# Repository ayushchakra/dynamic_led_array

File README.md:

develoment steps:
1. create very basic tester board with serial connections, USBASP connections, and some debug LEDs. this will validate the USBasp pipeline(first test with the arduino IDE), and then enable us to test with the rust toolchain - also might be nice to include a small version of the programmable led array
2. in parallel, develop the schematic for the final PCB, not shipping it until phase 1. PCB has been fully validated

- phase 1 also serves as a tester platformthat can be used while debugging any hardware issues with phase 2. (essentially, instead of hardware commands, send the corresponding action over serial, this can be intercepted by a hardware visualizer on a computer to "simulate" the hardware

- phase 1 can use the LED Driver eval board (just one) with one LED array to serve as a testing platform, for future iterations, the chip can be integrated into the carrier board

LED array options:
|Link	|Communication Protocol	|Price|Daisy Chain?|
|-------|-----------------------|-----|------------|
[16x16](https://www.amazon.com/BTF-LIGHTING-Individual-Addressable-Flexible-Controllers/dp/B088BTYJH6/ref=asc_df_B088BTYJH6/?tag=hyprod-20&linkCode=df0&hvadid=647362028828&hvpos=&hvnetw=g&hvrand=5458167644642167462&hvpone=&hvptwo=&hvqmt=&hvdev=c&hvdvcmdl=&hvlocint=&hvlocphy=9003506&hvtargid=pla-1007368042799&mcid=40403d086ed33ef990504ed588694c3e&th=1)| Unknown | 18.99|
[9x16](https://www.digikey.com/en/products/detail/adafruit-industries-llc/2947/5959341)| I2C | 

- [LED matrix](https://www.digikey.com/en/products/detail/adafruit-industries-llc/2973/5959350)
- [LED driver eval board](https://www.digikey.com/en/products/detail/adafruit-industries-llc/2946/5959340?utm_adgroup=&utm_source=google&utm_medium=cpc&utm_campaign=Pmax_Shopping_Boston%20Metro%20Category%20Awarness&utm_term=&utm_content=&utm_id=go_cmp-20837509568_adg-_ad-__dev-c_ext-_prd-5959340_sig-Cj0KCQiAm4WsBhCiARIsAEJIEzU_WlsF7jv6vVdvdmGJQAAfPQx7lVcIfZWQJUs7w_8XBYPrdWWNItYaAvw1EALw_wcB&gad_source=1&gclid=Cj0KCQiAm4WsBhCiARIsAEJIEzU_WlsF7jv6vVdvdmGJQAAfPQx7lVcIfZWQJUs7w_8XBYPrdWWNItYaAvw1EALw_wcB)
- [LED driver chip](https://www.digikey.com/en/products/detail/lumissil-microsystems/IS31FL3731-QFLS2-TR/4286473)

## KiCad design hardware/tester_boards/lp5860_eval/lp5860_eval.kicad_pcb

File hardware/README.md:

currently operating on the assumption that the mcu will be a atmega328pb

required secondary devices:
programmable LED array (preferably over i2c)
imu
speaker

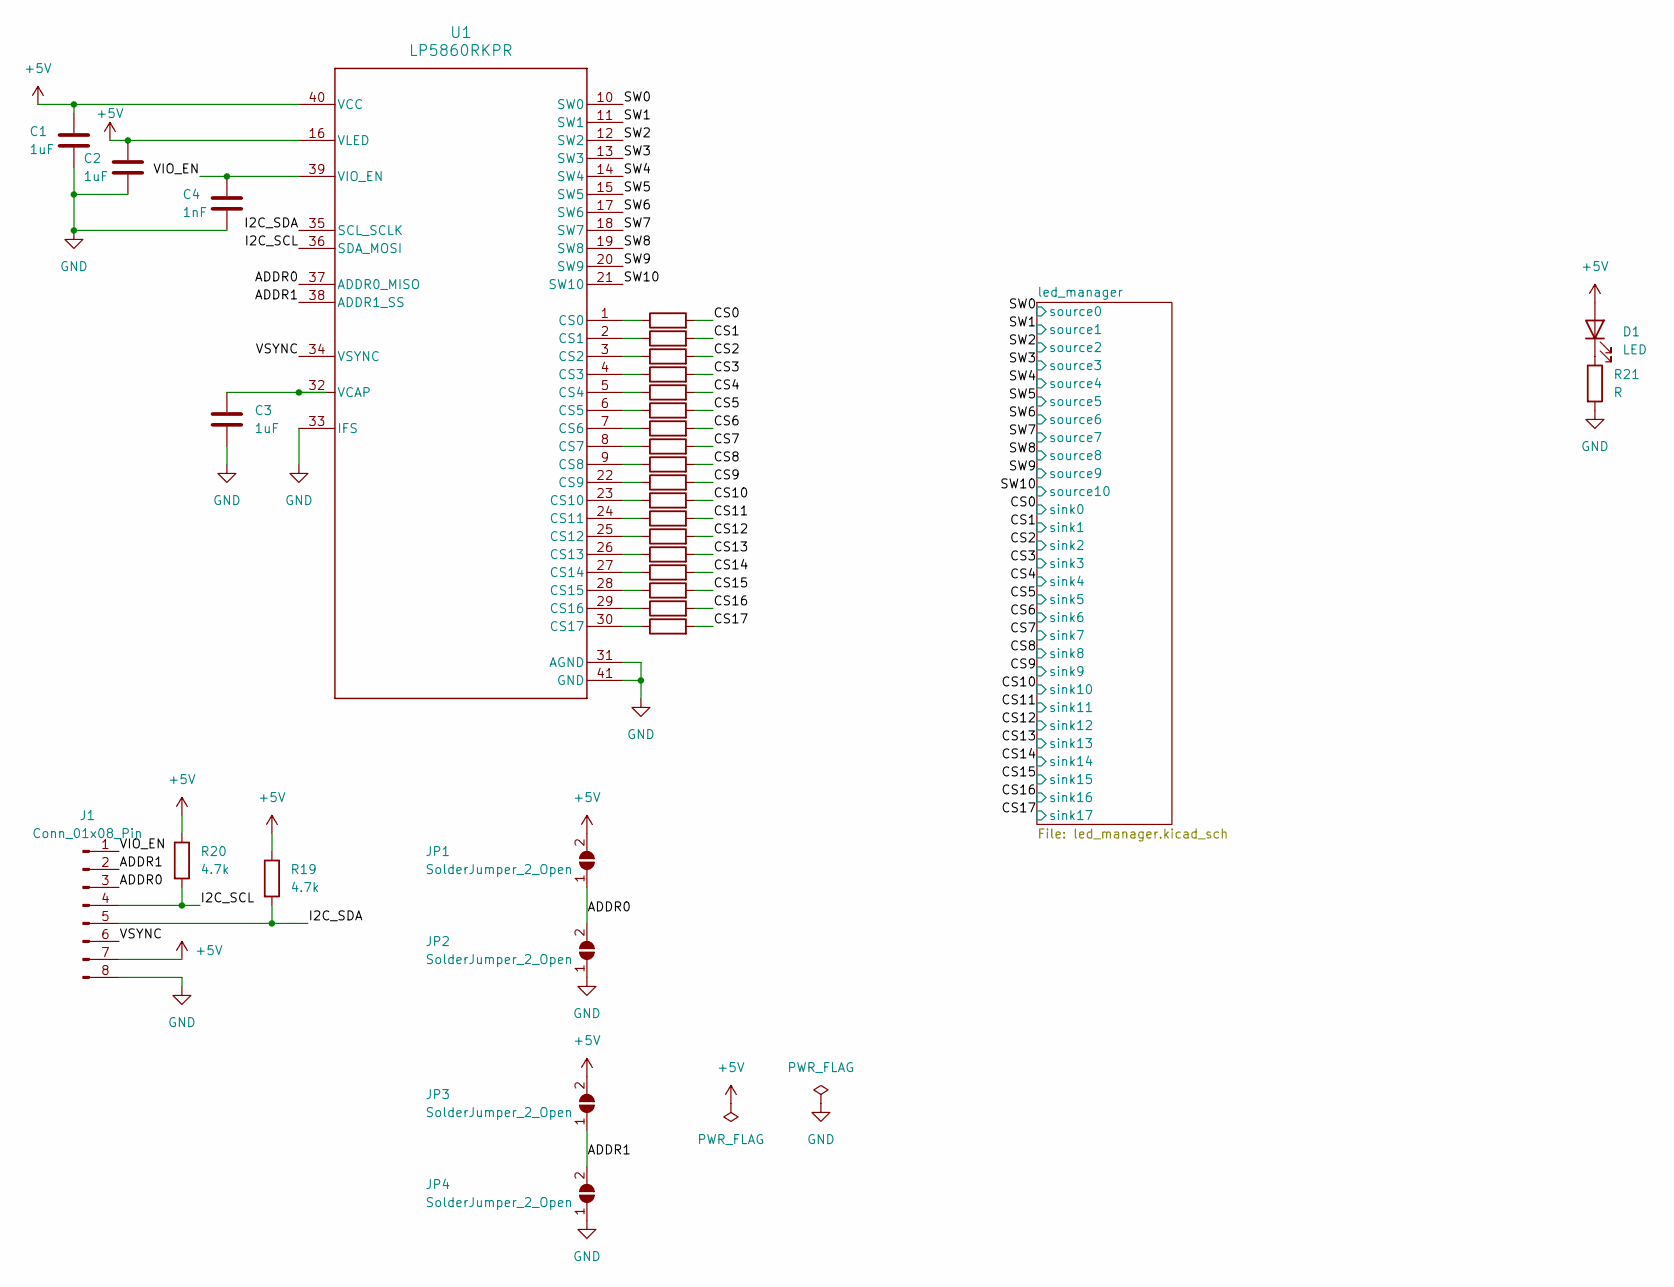
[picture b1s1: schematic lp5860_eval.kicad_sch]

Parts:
C1, C2, C3: 1uF; C_0603_1608Metric
C4: 1nF; C_0603_1608Metric
D1: LED; LED_0805_2012Metric
J1: Conn_01x08_Pin; PinHeader_1x08_P2.54mm_Vertical
JP1, JP2, JP3, JP4: SolderJumper_2_Open; SolderJumper-2_P1.3mm_Open_Pad1.0x1.5mm
R1, R2, R3, R4, R5, R6, R7, R8, R9, R10, R11, R12, R13, R14, R15, R16, R17, R18, R21: R; R_0603_1608Metric
R19, R20: 4.7k; R_0603_1608Metric
U1: LP5860RKPR; lp5860

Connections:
+5V: C1.1, C2.1, D1.2 (A), J1.7, JP1.2 (B), JP3.2 (B), R19.1, R20.1, U1.16 (VLED), U1.40 (VCC)
/ADDR0: J1.3, JP1.1 (A), JP2.2 (B), U1.37 (ADDR0_MISO)
/ADDR1: J1.2, JP3.1 (A), JP4.2 (B), U1.38 (ADDR1_SS)
/CS0: R18.2; also elsewhere on the board
/CS1: R17.2; also elsewhere on the board
/CS2: R16.2; also elsewhere on the board
/CS3: R15.2; also elsewhere on the board
/CS4: R14.2; also elsewhere on the board
/CS5: R13.2; also elsewhere on the board
/CS6: R12.2; also elsewhere on the board
/CS7: R11.2; also elsewhere on the board
/CS8: R10.2; also elsewhere on the board
/CS9: R9.2; also elsewhere on the board
/CS10: R8.2; also elsewhere on the board
/CS11: R7.2; also elsewhere on the board
/CS12: R6.2; also elsewhere on the board
/CS13: R5.2; also elsewhere on the board
/CS14: R4.2; also elsewhere on the board
/CS15: R3.2; also elsewhere on the board
/CS16: R2.2; also elsewhere on the board
/CS17: R1.2; also elsewhere on the board
/I2C_SCL: J1.4, R20.2, U1.36 (SDA_MOSI)
/I2C_SDA: J1.5, R19.2, U1.35 (SCL_SCLK)
/SW0: U1.10 (SW0); also elsewhere on the board
/SW1: U1.11 (SW1); also elsewhere on the board
/SW2: U1.12 (SW2); also elsewhere on the board
/SW3: U1.13 (SW3); also elsewhere on the board
/SW4: U1.14 (SW4); also elsewhere on the board
/SW5: U1.15 (SW5); also elsewhere on the board
/SW6: U1.17 (SW6); also elsewhere on the board
/SW7: U1.18 (SW7); also elsewhere on the board
/SW8: U1.19 (SW8); also elsewhere on the board
/SW9: U1.20 (SW9); also elsewhere on the board
/SW10: U1.21 (SW10); also elsewhere on the board
/VIO_EN: C4.1, J1.1, U1.39 (VIO_EN)
/VSYNC: J1.6, U1.34 (VSYNC)
GND: C1.2, C2.2, C3.2, C4.2, J1.8, JP2.1 (A), JP4.1 (A), R21.2, U1.31 (AGND), U1.33 (IFS), U1.41 (GND)
unnamed: D1.1 (K), R21.1
unnamed: R18.1, U1.1 (CS0)
unnamed: R17.1, U1.2 (CS1)
unnamed: R16.1, U1.3 (CS2)
unnamed: R15.1, U1.4 (CS3)
unnamed: R14.1, U1.5 (CS4)
unnamed: R13.1, U1.6 (CS5)
unnamed: R12.1, U1.7 (CS6)
unnamed: R11.1, U1.8 (CS7)
unnamed: R10.1, U1.9 (CS8)
unnamed: R9.1, U1.22 (CS9)
unnamed: R8.1, U1.23 (CS10)
unnamed: R7.1, U1.24 (CS11)
unnamed: R6.1, U1.25 (CS12)
unnamed: R5.1, U1.26 (CS13)
unnamed: R4.1, U1.27 (CS14)
unnamed: R3.1, U1.28 (CS15)
unnamed: R2.1, U1.29 (CS16)
unnamed: R1.1, U1.30 (CS17)
unnamed: C3.1, U1.32 (VCAP)

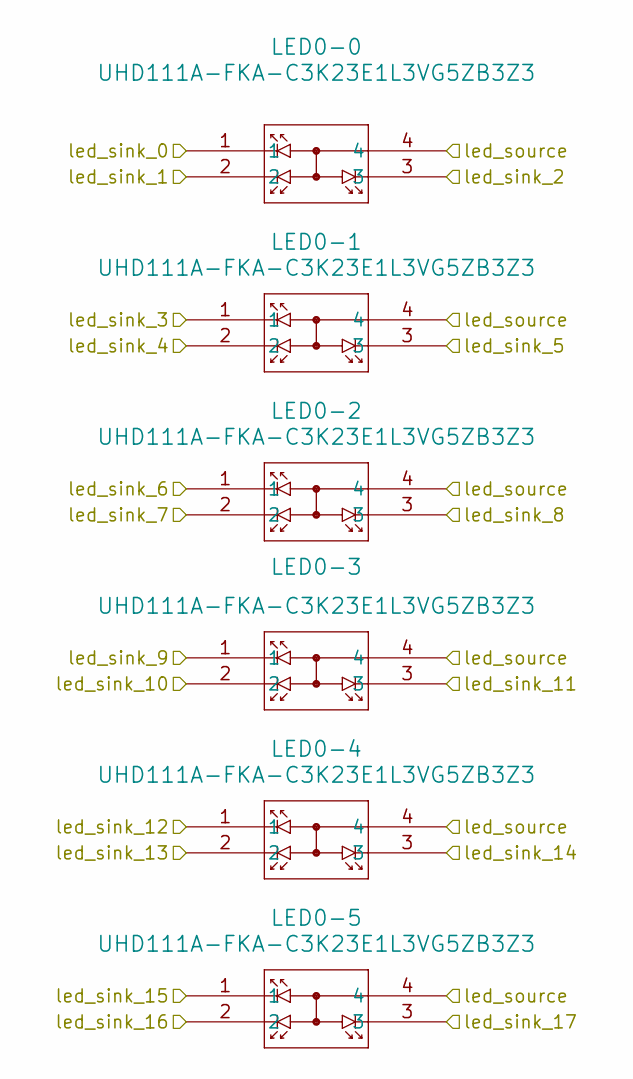
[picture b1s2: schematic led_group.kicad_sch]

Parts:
LED0-0, LED0-1, LED0-2, LED0-3, LED0-4, LED0-5: UHD111A-FKA-C3K23E1L3VG5ZB3Z3; rgb_led

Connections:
/CS0: LED0-0.1; also elsewhere on the board
/CS1: LED0-0.2; also elsewhere on the board
/CS2: LED0-0.3; also elsewhere on the board
/CS3: LED0-1.1; also elsewhere on the board
/CS4: LED0-1.2; also elsewhere on the board
/CS5: LED0-1.3; also elsewhere on the board
/CS6: LED0-2.1; also elsewhere on the board
/CS7: LED0-2.2; also elsewhere on the board
/CS8: LED0-2.3; also elsewhere on the board
/CS9: LED0-3.1; also elsewhere on the board
/CS10: LED0-3.2; also elsewhere on the board
/CS11: LED0-3.3; also elsewhere on the board
/CS12: LED0-4.1; also elsewhere on the board
/CS13: LED0-4.2; also elsewhere on the board
/CS14: LED0-4.3; also elsewhere on the board
/CS15: LED0-5.1; also elsewhere on the board
/CS16: LED0-5.2; also elsewhere on the board
/CS17: LED0-5.3; also elsewhere on the board
/SW0: LED0-0.4, LED0-1.4, LED0-2.4, LED0-3.4, LED0-4.4, LED0-5.4; also elsewhere on the board

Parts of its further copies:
LED1-0, LED1-1, LED1-2, LED1-3, LED1-4, LED1-5, LED2-0, LED2-1, LED2-2, LED2-3, LED2-4, LED2-5, LED3-0, LED3-1, LED3-2, LED3-3, LED3-4, LED3-5, LED4-0, LED4-1, LED4-2, LED4-3, LED4-4, LED4-5, LED5-0, LED5-1, LED5-2, LED5-3, LED5-4, LED5-5, LED6-0, LED6-1, LED6-2, LED6-3, LED6-4, LED6-5, LED7-0, LED7-1, LED7-2, LED7-3, LED7-4, LED7-5, LED8-0, LED8-1, LED8-2, LED8-3, LED8-4, LED8-5, LED9-0, LED9-1, LED9-2, LED9-3, LED9-4, LED9-5, LED10-0, LED10-1, LED10-2, LED10-3, LED10-4, LED10-5: UHD111A-FKA-C3K23E1L3VG5ZB3Z3; rgb_led

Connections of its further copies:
/CS0: LED1-0.1, LED2-0.1, LED3-0.1, LED4-0.1, LED5-0.1, LED6-0.1, LED7-0.1, LED8-0.1, LED9-0.1, LED10-0.1; also elsewhere on the board
/CS1: LED1-0.2, LED2-0.2, LED3-0.2, LED4-0.2, LED5-0.2, LED6-0.2, LED7-0.2, LED8-0.2, LED9-0.2, LED10-0.2; also elsewhere on the board
/CS2: LED1-0.3, LED2-0.3, LED3-0.3, LED4-0.3, LED5-0.3, LED6-0.3, LED7-0.3, LED8-0.3, LED9-0.3, LED10-0.3; also elsewhere on the board
/CS3: LED1-1.1, LED2-1.1, LED3-1.1, LED4-1.1, LED5-1.1, LED6-1.1, LED7-1.1, LED8-1.1, LED9-1.1, LED10-1.1; also elsewhere on the board
/CS4: LED1-1.2, LED2-1.2, LED3-1.2, LED4-1.2, LED5-1.2, LED6-1.2, LED7-1.2, LED8-1.2, LED9-1.2, LED10-1.2; also elsewhere on the board
/CS5: LED1-1.3, LED2-1.3, LED3-1.3, LED4-1.3, LED5-1.3, LED6-1.3, LED7-1.3, LED8-1.3, LED9-1.3, LED10-1.3; also elsewhere on the board
/CS6: LED1-2.1, LED2-2.1, LED3-2.1, LED4-2.1, LED5-2.1, LED6-2.1, LED7-2.1, LED8-2.1, LED9-2.1, LED10-2.1; also elsewhere on the board
/CS7: LED1-2.2, LED2-2.2, LED3-2.2, LED4-2.2, LED5-2.2, LED6-2.2, LED7-2.2, LED8-2.2, LED9-2.2, LED10-2.2; also elsewhere on the board
/CS8: LED1-2.3, LED2-2.3, LED3-2.3, LED4-2.3, LED5-2.3, LED6-2.3, LED7-2.3, LED8-2.3, LED9-2.3, LED10-2.3; also elsewhere on the board
/CS9: LED1-3.1, LED2-3.1, LED3-3.1, LED4-3.1, LED5-3.1, LED6-3.1, LED7-3.1, LED8-3.1, LED9-3.1, LED10-3.1; also elsewhere on the board
/CS10: LED1-3.2, LED2-3.2, LED3-3.2, LED4-3.2, LED5-3.2, LED6-3.2, LED7-3.2, LED8-3.2, LED9-3.2, LED10-3.2; also elsewhere on the board
/CS11: LED1-3.3, LED2-3.3, LED3-3.3, LED4-3.3, LED5-3.3, LED6-3.3, LED7-3.3, LED8-3.3, LED9-3.3, LED10-3.3; also elsewhere on the board
/CS12: LED1-4.1, LED2-4.1, LED3-4.1, LED4-4.1, LED5-4.1, LED6-4.1, LED7-4.1, LED8-4.1, LED9-4.1, LED10-4.1; also elsewhere on the board
/CS13: LED1-4.2, LED2-4.2, LED3-4.2, LED4-4.2, LED5-4.2, LED6-4.2, LED7-4.2, LED8-4.2, LED9-4.2, LED10-4.2; also elsewhere on the board
/CS14: LED1-4.3, LED2-4.3, LED3-4.3, LED4-4.3, LED5-4.3, LED6-4.3, LED7-4.3, LED8-4.3, LED9-4.3, LED10-4.3; also elsewhere on the board
/CS15: LED1-5.1, LED2-5.1, LED3-5.1, LED4-5.1, LED5-5.1, LED6-5.1, LED7-5.1, LED8-5.1, LED9-5.1, LED10-5.1; also elsewhere on the board
/CS16: LED1-5.2, LED2-5.2, LED3-5.2, LED4-5.2, LED5-5.2, LED6-5.2, LED7-5.2, LED8-5.2, LED9-5.2, LED10-5.2; also elsewhere on the board
/CS17: LED1-5.3, LED2-5.3, LED3-5.3, LED4-5.3, LED5-5.3, LED6-5.3, LED7-5.3, LED8-5.3, LED9-5.3, LED10-5.3; also elsewhere on the board
/SW1: LED1-0.4, LED1-1.4, LED1-2.4, LED1-3.4, LED1-4.4, LED1-5.4; also elsewhere on the board
/SW2: LED2-0.4, LED2-1.4, LED2-2.4, LED2-3.4, LED2-4.4, LED2-5.4; also elsewhere on the board
/SW3: LED4-0.4, LED4-1.4, LED4-2.4, LED4-3.4, LED4-4.4, LED4-5.4; also elsewhere on the board
/SW4: LED10-0.4, LED10-1.4, LED10-2.4, LED10-3.4, LED10-4.4, LED10-5.4; also elsewhere on the board
/SW5: LED3-0.4, LED3-1.4, LED3-2.4, LED3-3.4, LED3-4.4, LED3-5.4; also elsewhere on the board
/SW6: LED9-0.4, LED9-1.4, LED9-2.4, LED9-3.4, LED9-4.4, LED9-5.4; also elsewhere on the board
/SW7: LED5-0.4, LED5-1.4, LED5-2.4, LED5-3.4, LED5-4.4, LED5-5.4; also elsewhere on the board
/SW8: LED6-0.4, LED6-1.4, LED6-2.4, LED6-3.4, LED6-4.4, LED6-5.4; also elsewhere on the board
/SW9: LED8-0.4, LED8-1.4, LED8-2.4, LED8-3.4, LED8-4.4, LED8-5.4; also elsewhere on the board
/SW10: LED7-0.4, LED7-1.4, LED7-2.4, LED7-3.4, LED7-4.4, LED7-5.4; also elsewhere on the board

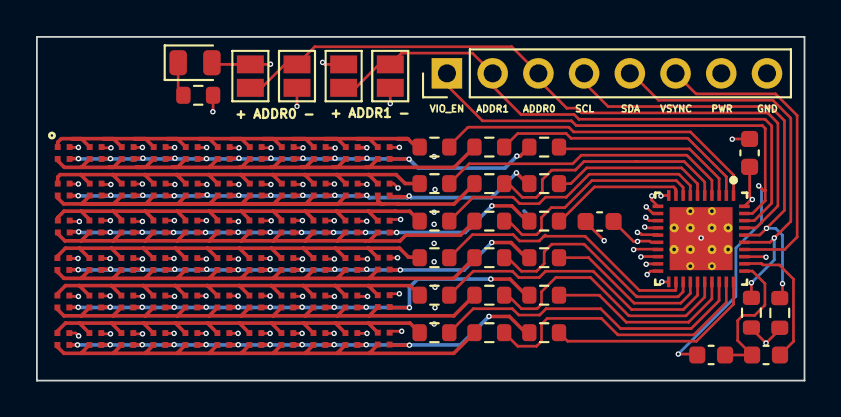
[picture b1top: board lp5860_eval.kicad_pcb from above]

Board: 4 copper layers, 42.6 x 19.1 mm, 98 parts (0 on the bottom side), 57 nets.

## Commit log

2023-12-20 basic readme
2023-12-20 researched led drivers
2024-03-15 started sil playground
2024-03-25 added led and led driver datasheets
2024-03-25 initial schematic of lp5860 tester board
2024-03-26 initial layout
